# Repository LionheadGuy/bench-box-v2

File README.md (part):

# Bench Box V2

A portable, battery-powered workstation built around an **ODROID-H5** and a **10.1" touchscreen** in a 3D-printed
case with a carry handle. Think of it as a chunky, repairable laptop: USB-C charging, about 3 hours on its own battery,
its own USB 3 hub, WiFi 6E, optional LTE, and a dock for an Elgato Stream Deck module.

It was made for developing car infotainment systems on the bench (it runs the same x86 computer the car does), but
nothing in it is car-specific: it is a general-purpose Windows or Linux PC.

| | |
|---|---|
| Computer | ODROID-H5 (Intel Core i3-N300, 8 cores), 16 GB DDR5, NVMe SSD |
| Screen | 10.1" 1280 x 800 IPS touchscreen, flush in the front frame |
| Battery | 14.8 V 6.6 Ah LiPo (~98 Wh) with a smart BMS; ~3 h at a typical 30 W |
| Charging | USB-C PD (60 W+ charger; 100 W for the fastest charge), runs while charging, no break when unplugged |
| USB | 4 x USB-A on the back: three on the box's own hub board, one wired straight through to a spare port on the computer; plus header ports used inside for the Stream Deck |
| Network | Ethernet on a keystone jack in the back wall |
| Wireless | WiFi 6E + Bluetooth (Intel AX210); optional LTE Cat 6 (Quectel EM060K); optional Bluetooth hands-free board (calls, phone book, phone audio) |
| Cooling | 3 Noctua fans (one in, two out), on the H5's own fan control |
| Size | about 280 x 227 x 116 mm (W x H x D, Stream Deck dock included) + 44 mm handle |
| Weight | about 2.7 kg (estimate) |

> ## Status: read this first
>
> **The design is complete, but this exact version has not been built yet.** The first version of the box (same
> computer, screen, fans and mounting, mains-powered) was printed and works. Version 2 adds the battery, the custom
> charger and converter boards, a new hub and a new shell; its parts have been checked against each other in CAD
> (no collisions) but not printed or wired up. The custom boards are designed and checked against their datasheets,
> not yet built; they will be available from the builder, assembled (price to be announced). This page will be updated
> as the first V2 is built.
>
> **Lithium safety**: the pack is a large LiPo with no protection of its own. Never connect it without the BMS, keep
> it in a fireproof LiPo sleeve, charge it where you can watch it until you trust the build, and test new boards on a
> current-limited bench supply first.

## Pictures (CAD)

| Back | Inside (shell hidden, from behind) |
|---|---|
|  |  |

## What's here

| Folder | What |
|---|---|
| [`print/`](print) | **Slicer-ready `.3mf` files**, one per print job, parts already laid flat |
| [`stl/`](stl) | the same parts as STL, in their assembled positions (GitHub shows them in 3D) |
| [`bom.csv`](bom.csv) | the parts list below as a spreadsheet |
| [`wiring/`](wiring) | wiring poster (`bench-box-v2-poster.png` / `.pdf`) and wire-by-wire sheets (open `index.html`; `wirelist.csv` lists every lead) |
| [`images/`](images) | the pictures on this page |

## Bill of materials

**Roughly $1,350 for the core build's bought parts** (estimate, without the screen's price, which varies, and without
the custom boards, whose price is to be announced), plus about $140 for the Stream Deck dock and $150 for LTE. Prices are approximate (USD, November 2026) and change; links are to the maker or a major seller. "x2" etc. is how
many the box uses.

### Computer

| Part | Qty | For | Price | Notes |
|---|---|---|---|---|
| [Hardkernel ODROID-H5](https://www.hardkernel.com/shop/odroid-h5/) | 1 | the computer | $230 | no power adapter needed; ships from Korea |
| [16 GB DDR5 SODIMM (Corsair CMSX16GX5M1A5600C48)](https://www.centralcomputer.com/corsair-cmsx16gx5m1a5600c48-16gb-16gbx1-ddr5-so-dimm-laptop-memory.html) | 1 | RAM | ~$220-250 | any single DDR5 SODIMM works; runs at 4800 |
| [M.2 2280 NVMe SSD (SanDisk Optimus 5100 500 GB)](https://www.cdw.com/product/sandisk-optimus-5100-ssd-500-gb-pcie-4.0-x4-nvme/9205163) | 1 | storage, slot M2_SSD1 | ~$118 | any M.2 2280 NVMe |
| [Intel AX210NGW WiFi 6E + Bluetooth card](https://www.amazon.com/dp/B08MJLPZPL) | 1 | WiFi | ~$20-25 |  |
| [M.2 M-key to A/E-key adapter (HighZer0)](https://www.amazon.com/dp/B0BGCWQY67) | 1 | puts the AX210 in slot M2_SSD4 | ~$12-15 | the H5 has only M-key slots |
| [Tenmory WiFi 6E antenna kit (2 RP-SMA antennas + 2 MHF4 pigtails)](https://www.amazon.com/dp/B07QDZKH5N) | 1 | WiFi antennas | ~$15 | pigtails go to the back-wall WiFi holes |

### Screen and controls

| Part | Qty | For | Price | Notes |
|---|---|---|---|---|
| [VIEWMEI 10.1" 1280 x 800 USB-C touchscreen](https://www.amazon.com/dp/B0GCNXNZ17) | 1 | main screen | check listing | the frame is sized to this screen: 245.5 x 168.75 x 21.5 mm, 75 mm VESA (M4). Check the size before buying |
| [12 mm momentary metal push button, 5 V ring LED](https://www.amazon.com/s?k=12mm+momentary+metal+push+button+5V+ring+LED) | 1 | power button | ~$5-8 | 11.75 mm hole; NO contacts + LED |
| [KCD1 rocker switch, 20 A (Dopkiut, 10-pack)](https://www.amazon.com/dp/B0HCZ5X637) | 1 | master power switch | $6 | 19.2 x 12.7 mm cut-out |

### Battery and charging

| Part | Qty | For | Price | Notes |
|---|---|---|---|---|
| [Liperior Endurance 6600 mAh 4S2P LiPo (LPD66004S150)](https://rcbattery.com/liperior-endurance-6600mah-4s2p-150c-14-8v-speed-runs-lipo-battery.html) | 1 | the pack, ~98 Wh | $69.99 | 135 x 54 x 42 mm, bare 7 AWG leads, no protection of its own |
| [JBD SP04S010A smart BMS, 4S, NMC / Li-ion version, 20 A or 30 A](https://jbdbms.com/products/sp04s010a) | 1 | protection and balancing | ~$17.50 | pick the NMC (Li-ion) 4S version; add the Bluetooth module for the phone app |
| [LiPo safety bag (DerBlue, 185 x 75 x 60 mm)](https://www.amazon.com/dp/B01GCHBQJS) | 1 | fire sleeve round the pack | ~$8-10 |  |
| [Inline ATC/ATO fuse holder, 14 AWG, + 10 A fuse](https://www.amazon.com/s?k=inline+ATC+fuse+holder+14+AWG) | 1 | pack + lead | ~$6 |  |
| [Semitec 103AT-2 10 k NTC thermistor](https://www.digikey.com/en/products/result?keywords=103AT-2) | 1 | pack temperature for the charger | $0.68 | tape it to the pack |
| [JST PH 2-pin pigtails (pack of 10)](https://www.amazon.com/s?k=JST+PH+2.0+2+pin+pigtail) | 1 | NTC to charger J4 | ~$6 |  |
| [Amass XT30-U connector pairs (5 pairs)](https://www.getfpv.com/amass-xt30-u-lipo-connector-set-5-pairs.html) | 1 | all power leads | ~$8 |  |
| [100 W USB-C PD charger (Anker Prime 100 W or UGREEN Nexode 100 W)](https://www.amazon.com/dp/B0963HDMJP) | 1 | charges and runs the box | ~$50-70 | any USB-C PD charger with 20 V; 60 W minimum |
| [USB-C cable, 5 A e-marked (Anker 100 W)](https://www.amazon.com/dp/B072JYDQ7N) | 1 | charger to box | ~$15-20 | needed for the 100 W setting (JP1 cut) |

### Custom boards (from the builder)

Designed for this box and sold assembled by the builder; prices are to be announced. What each board does and how it
connects: [Custom boards](#custom-boards) below.

| Part | Qty | For | Price | Notes |
|---|---|---|---|---|
| Hub board | 1 | the USB ports on the back, and the battery readout | TBD | from the builder |
| Charger board | 1 | USB-C in, charging, power path | TBD | from the builder |
| Converter board | 1 | fuses + 12 V for the H5 | TBD | from the builder; fuses not included (below) |
| [Littelfuse 0297010.WXNV MINI blade fuse, 10 A](https://www.digikey.com/en/products/result?keywords=0297010.WXNV) | 1+ | converter board F2 | $0.39 | buy spares |
| [Littelfuse 0297005.WXNV MINI blade fuse, 5 A](https://www.digikey.com/en/products/result?keywords=0297005.WXNV) | 1+ | converter board F1 | $0.39 | buy spares |

### USB and cables

| Part | Qty | For | Price | Notes |
|---|---|---|---|---|
| [HDMI, 1 ft, 90 degree plug](https://www.amazon.com/dp/B06Y69TCTW) | 1 | H5 to screen | ~$8-10 |  |
| [USB-A to USB-C, 1 ft, right-angle (2-pack)](https://www.amazon.com/dp/B0784F9JP2) | 1 | H5 USB 2.0 to the screen (power + touch), and H5 USB 3.0 to the hub board | ~$8 | the 2-pack covers both |
| [USB-A to JST PH 4-pin lead](https://www.amazon.com/s?k=usb+a+to+jst+ph+4+pin+cable) | 1 | the back's pass-through port to a spare H5 USB 2.0 port | ~$5 | check the lead's pin order against the board before plugging it in |
| [18 AWG pigtail, 5.5 x 2.1 mm male barrel (3-pack)](https://www.amazon.com/dp/B0DGQS55NG) | 1 | converter 12 V to the H5 | $6.99 | fit an XT30 male on the free end |
| [Cat6 UTP punch-down keystone jack](https://www.amazon.com/s?k=cat6+utp+punch+down+keystone+jack) | 1 | Ethernet port in the back wall | ~$5 | standard keystone (14.9 x 19.4 mm opening); unshielded |
| [Cat6 patch cable, 1 ft](https://www.amazon.com/s?k=cat6+patch+cable+1+ft) | 1 | H5 to the keystone jack | ~$5 | far end cut off and punched down on the jack |
| [JST PH 4-pin lead, 200 mm](https://www.amazon.com/s?k=jst+ph+2.0+4+pin+cable) | 1 | hub board to the BMS's UART plug (battery readout) | ~$5 | check the BMS's pin order before plugging it in |

### Cooling

| Part | Qty | For | Price | Notes |
|---|---|---|---|---|
| [Noctua NF-A9x14 PWM](https://www.amazon.com/dp/B009NQM7V2) | 1 | intake, back wall | $18.95 |  |
| [Noctua NF-A6x15 PWM (12 V version)](https://www.amazon.com/dp/B0DJNX4CX4) | 2 | exhaust, top | $16.95 each | not the 5 V version |
| [Noctua 3-way 4-pin PWM splitter (NA-SC1)](https://www.amazon.com/dp/B0DJPBXZ89) | 1 | three fans on the H5 fan header | ~$10 |  |

### Screws, inserts, small parts

| Part | Qty | For | Price | Notes |
|---|---|---|---|---|
| [ruthex M3 heat-set inserts (100)](https://www.amazon.com/dp/B08BCRZZS3) | 33 used (37 with the Bluetooth board) | all M3 mounts | $9.99 | 4.0 mm holes as printed |
| [ruthex M2 heat-set inserts](https://www.amazon.com/dp/B088QJG676) | 8 used | BMS + modem | ~$9-10 |  |
| [M3 button-head screw kit (Besitu, 6-35 mm)](https://www.amazon.com/dp/B0D1KQCBMT) | 1 | M3 x 6 (8), x 8 (17, +4 for the Bluetooth board), x 10 (8) | $21.99 | button heads: the holes have no countersinks |
| [M4 x 8 button-head screws](https://www.amazon.com/dp/B0FGX64FW2) | 4 | screen VESA | ~$21 (kit) | check the screen's thread depth first |
| [M2 screws: 4 x M2 x 6 + 4 long (length to suit the BMS)](https://www.amazon.com/s?k=M2+button+head+screw+kit) | 8 | modem board, BMS | ~$10 | BMS screws go through cover, board and base plate |
| [Hook-and-loop straps, 20 mm wide](https://www.amazon.com/s?k=20mm+hook+and+loop+battery+strap) | 2 | hold the pack | ~$7 |  |
| [Stick-on rubber feet](https://www.amazon.com/dp/B07PWCC6KP) | 4 | under the feet | $7.99 |  |

### Wire and connectors

| Part | Qty | For | Price | Notes |
|---|---|---|---|---|
| [14 AWG silicone wire, red + black](https://www.amazon.com/s?k=14+awg+silicone+wire+red+black) | 1 | battery path | ~$12 |  |
| [18 AWG silicone pair, tinned copper (BNTECHGO)](https://www.amazon.com/dp/B0779QRR58) | 1 | hub and 12 V leads | $14.83 |  |
| [Dupont crimp kit (housings + pins + crimper)](https://www.amazon.com/s?k=dupont+crimp+kit) | 1 | header connections | ~$25 |  |
| [Heat-shrink kit](https://www.amazon.com/dp/B0C81FHPHN) | 1 | every joint | $9.99 |  |

### Printing

| Part | Qty | For | Price | Notes |
|---|---|---|---|---|
| [ASA or ABS filament, 1 kg](https://www.amazon.com/s?k=ASA+filament+1kg) | 1 | all printed parts | ~$25 | PETG for a desk-only box |

### Optional: Stream Deck dock

| Part | Qty | For | Price | Notes |
|---|---|---|---|---|
| [Elgato Stream Deck Module 15 Keys (10GBT9901)](https://www.elgato.com/us/en/p/stream-deck-module-15-keys) | 1 | 15 LCD keys, docked on the right wall | $129.99 | case (122 x 83 x 24 mm): print/5-stream-deck-case.3mf + 4 x M3 x 6 and 4 inserts |
| [Coiled USB-C to USB-A cable (Cable Matters 4 ft)](https://cablematters.com/pc-1678-123-coiled-usb-c-to-usb-a-charging-cable-4ft.aspx) | 1 | Stream Deck to header port P7 | ~$10-13 | USB-A end cut off; thread the bare wires through the case and the shell before crimping them, as both holes are printed small |

### Optional: LTE

| Part | Qty | For | Price | Notes |
|---|---|---|---|---|
| [Quectel EM060K-GL LTE Cat 6 M.2 module](https://www.waveshare.com/product/em060k-gl.htm) | 1 | mobile data | $98.99 |  |
| [Waveshare USB to M.2 B-key board](https://www.waveshare.com/usb-to-m.2-b-key.htm) | 1 | carries the module (USB) | ~$22 | CUT 58 mm from its USB end (removes its SMA jacks) to fit the mount; file the edge and check for shorts |
| LTE modem board (coming) | 1 | the builder's own carrier for the module, in place of the Waveshare board | TBD | from the builder; same size and holes as the cut Waveshare board, so it uses the same four standoffs (JST end up); USB on a JST PH 4-pin lead, no USB-A plug or extension |
| [MHF4 to SMA female bulkhead pigtails, 20 cm (2-pack)](https://www.amazon.com/dp/B0FVW7M3LC) | 1 | module to the back-wall LTE holes | $7.49 |  |
| [LTE antennas, SMA male](https://www.amazon.com/s?k=LTE+antenna+SMA+male) | 2 | on the LTE holes | ~$15 |  |
| Nano SIM with a data plan that allows modems | 1 |  |  | many phone plans do not allow modem use |

### Optional: Bluetooth hands-free board

| Part | Qty | For | Price | Notes |
|---|---|---|---|---|
| Bluetooth board | 1 | phone calls, phone book and phone music (Feasycom FSC-BT1026C module), as a COM port + a USB sound card on one USB lead | TBD | from the builder |
| [JST PH 2.0 pigtails, 2 / 3 / 4-pin (assorted)](https://www.amazon.com/s?k=JST+PH+2.0+pigtail+assortment) | 1 set | the board's USB lead (4-pin, to header port P6), mic (2-pin) and line out (3-pin) | ~$8 | |
| [3.5 mm stereo panel-mount socket, M6 nut](https://www.amazon.com/s?k=3.5mm+panel+mount+stereo+jack+socket) | 2 | mic in + line out on the back wall | ~$6 | 6.5 mm holes as printed; check the thread before printing |
| [Hands-free car-kit microphone, 3.5 mm plug](https://www.amazon.com/s?k=car+hands+free+microphone+3.5mm) | 1 | the call microphone | ~$8-10 | plugs into the mic socket on the back |

### Optional: dash screen

| Part | Qty | For | Price | Notes |
|---|---|---|---|---|
| [ROADOM 10.25" 1920 x 720 bar touchscreen](https://www.amazon.com/dp/B0H9RBHD2X) | 1 | second screen for gauge / dashboard layouts | check listing | its printed case and a video pass-through in the box are coming |

## Custom boards

Sold assembled by the builder (prices to be announced). They are designed and checked, **not yet built or tested**:
test the first ones on a current-limited bench supply, without the pack, before they go in a box.

**Hub board** (75.5 x 68 mm). The box's USB ports and the battery readout on one board, in place of an
off-the-shelf hub.

- **Three USB-A ports** on the back, from a 4-port USB 3.2 hub chip, each with its own current limit.
- **Upstream on USB-C**, to the computer's USB 3.0 port.
- **A fourth USB-A on the back is a pass-through**: it is not on the hub at all, only wired to a 4-pin plug inside, so
  one device (an audio interface, say) can run straight to a spare port on the computer instead of sharing the hub.
- **The battery readout is on the board**: an isolated USB-serial port with a 4-pin plug for the BMS's UART, so there
  is no dongle and no cut extension lead inside the box.
- **5 V for the ports is made on the board** from the box's 12-20.5 V rail.

**Charger board** (52 x 68 mm). USB-C in, battery charging and the box's power path, in place of a USB-C PD trigger, a
separate 4S charger and two ideal-diode modules.

- **USB-C in at 20 V**: asks any USB-C PD charger for 20 V.
- **4S lithium charging** at **16.4 V** (4.10 V per cell, kinder to a pack that is kept full) and **4.5 A**.
- **Input current limit**: it turns the charging down so the box (running + charging) never overloads the charger.
  As supplied **2.92 A** (any 60 W+ charger, any normal cable); **cut jumper JP1** for **4.38 A** (needs a 100 W charger
  AND a 5 A e-marked USB-C cable).
- **Power path**: the box runs from SYS out, from USB-C when plugged in and from the pack when not, with no break.
- **Battery temperature**: a 10 k NTC (103AT) taped to the pack, into J4, gives a 0-45 °C charge window. **It will not
  charge with nothing in J4.** For a bench test without the NTC, close JP2 (fixed 10 k; removes the temperature cut-out).
- **LEDs**: green = 20 V agreed, yellow = input OK, red = charging, green = full (all dark when running on the pack).
- **Connectors** (plugs from above): J1 USB-C (through the left wall), J2 XT30 male = battery (through the BMS and the
  pack fuse), J3 XT30 female = SYS out to the rocker switch, J4 NTC (JST PH 2-pin).
- Charge time, 6.6 Ah pack: about 1.5 h with the box off (JP1 cut, 100 W charger) or 2.5 h (as supplied).

**Converter board** (70 x 60 mm). Splits the power rail and makes the computer's 12 V.

```
IN (XT30 male, 12-21 V from the rocker switch)
 ├─ 5 A MINI blade fuse ──────────────────> HUB (XT30 female) -> USB hub power (7-24 V)
 └─ 10 A MINI blade fuse -> 12 V 5 A DC/DC -> 12 V OUT (XT30 female) -> ODROID-H5   ("12 V ON" LED)
```

The fuses are MINI (ATM) automotive blades, replaceable by hand; buy them separately (in the BOM).

**Bluetooth board** (optional, 60 x 48 mm). Phone calls, phone book and phone music on one USB lead to the H5: a
Feasycom FSC-BT1026C module, a COM port for its commands (no driver on Windows 10/11) and a USB sound card whose
input carries the phone's audio into the computer (the H5 has no audio input) and whose output is a spare line out.
Connectors (JST PH): J2 USB lead (1 = +5 V, 2 = D-, 3 = D+, 4 = GND), J3 cabin microphone (electret, 1 = +), J4 line
out (L, R, GND); J1 USB-C as an alternative to J2 (use one, not both). LEDs: blue blinks while pairing, green when
connected. Keep metal away from the module's antenna at the top edge.

**LTE modem board** (optional, coming). A carrier for the Quectel EM060K: the module plugs into its M.2 socket, a
nano-SIM holder sits beside it, and USB comes in on a JST PH 4-pin lead (1 = +5 V, 2 = D-, 3 = D+, 4 = GND), so there is
no USB-A plug or extension in the box. The antennas still clip onto the module itself. Same size (30 x 58 mm) and
holes as the cut Waveshare board; the SIM holder is on its back.

| Top | Back |
|---|---|
|  |  |

**All boards**: XT30 polarity: + is the **square end** of the housing; check with a meter before the first plug-in.
Mounting: M3 screws onto heat-set inserts in the printed box (M2 for the modem board).

## Printing

Any FDM printer. **The shell needs a bed of at least 285 x 230 mm** (a 300 mm class printer such as a Bambu H2D,
Prusa XL or a large Voron); everything else fits a 256 x 256 mm bed.

**Material: ASA or ABS** (the box gets warm inside and may sit in a car). PETG works for a desk-only box. PLA is not
recommended (softens around 55 °C). 0.2 mm layers, 4 walls, 15-25 % infill. About one 1 kg spool in all (estimate).

| File | Parts | Supports | Notes |
|---|---|---|---|
| `1-shell.3mf` | the shell (frame, walls, battery bay, mounts) | **yes, on build plate only** | prints on its back; the biggest print, roughly 7-9 h |
| `2-front-plate.3mf` | front plate (holds the screen and the H5) | no | face down |
| `3-handle-and-feet.3mf` | handle + 2 feet | no | on their sides |
| `4-screen-button-caps.3mf` | 5 screen button caps | try without; tree supports if the small lugs droop | tiny parts: brim helps |
| `5-stream-deck-case.3mf` | Stream Deck case tray + front frame | no | optional (only with the Stream Deck) |
| `6-stream-deck-cradle-test.3mf` | a piece of the shell's right wall with the Stream Deck cradle | yes | optional: print it first to check your Stream Deck case slides in before printing the whole shell |
| `7-keystone-test.3mf` | a piece of the shell's back wall with the Ethernet keystone frame | no | optional: print it first to check your keystone jack clips in, as makes differ slightly |

After printing: ream the Stream Deck cable holes to your cable - both the one in the case and the 4 mm one in the
shell's right wall are printed small on purpose - and clean up the screen button holes so the caps turn freely.

## Assembly

Tools: soldering iron with a heat-set insert tip, small screwdrivers / 2 mm hex key, Dupont crimper, wire stripper,
multimeter.

1. **Heat-set inserts.** M3: front plate (4 on the H5 standoffs, 5 in the screw tabs), shell (4 hub standoffs on the
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
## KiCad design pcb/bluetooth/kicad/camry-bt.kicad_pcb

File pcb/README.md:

# Custom boards

Three small boards made for the Bench Box V2 (the Bluetooth board is optional). Both are designed to be **made and assembled by PCBWay** (turnkey): every
part has an exact manufacturer part number in the BOM, so you upload three files and they build it.

> **Status: designed and checked in KiCad (ERC clean, DRC 0 errors, 0 unconnected), checked against the datasheets,
> but not yet built or tested.** The charger board charges a lithium pack. Have someone who knows power electronics
> look over the schematic before you order, and test the first board on a bench supply with a current limit, without the
> pack, before it goes in a box.

## Charger board (`charger/`)

USB-C in, battery charging and the box's power path, in one 52 x 68 mm board. It replaces a USB-C "PD trigger" module,
a separate 4S charger and two ideal-diode modules.

- **USB-C in at 20 V** (WCH CH224A asks any USB-C PD charger for 20 V).
- **4S lithium charging** (TI BQ24610): **16.4 V** (4.10 V per cell, kinder to a pack that is kept full), **4.5 A**
  charge, 0.3 A precharge and end of charge, ~9 h safety timer.
- **Input current limit**: the board measures the total current from the USB-C charger (box running + charging) and
  turns the charging down to stay under the limit, so the box can never overload the charger.
  - **As built: 2.92 A** (any 60 W+ USB-C charger, any normal cable).
  - **Cut jumper JP1: 4.38 A** (needs a 100 W charger AND a 5 A e-marked USB-C cable).
- **Power path**: the box runs from the board's SYS output: from USB-C when plugged in, from the pack when not, with no
  break in between.
- **Battery temperature**: a 10 k NTC (103AT) taped to the pack, into J4 (JST PH 2-pin), gives a 0-45 °C charge
  window. **It will not charge with nothing in J4.** For a bench test without the NTC, close JP2 (fixed 10 k; this
  removes the temperature cut-out).
- **LEDs**: green = 20 V agreed, yellow = input OK, red = charging, green = full (all dark when running on the pack).
- **Connectors** (all vertical, plugs from above): J1 USB-C (through the box's left wall), J2 XT30 male = battery
  (through the BMS and the pack fuse), J3 XT30 female = SYS out to the power switch, J4 NTC.
- Charge time, 6.6 Ah pack: about 1.5 h with the box off (JP1 cut, 100 W charger) or 2.5 h (as built); longer while
  the box runs.

### Ordering at PCBWay (PCB + assembly)

Upload `charger-gerbers.zip`, `charger-bom-pcbway.csv`, `charger-positions.csv`.

| Option | Value |
|---|---|
| Size / layers | 68 x 52 mm, **4 layers**, FR-4 TG150-160, 1.6 mm |
| Min track / spacing | **5 / 5 mil** |
| Min hole | **0.2 mm** |
| Copper | **1 oz outer, 1 oz inner** (do not pick 2 oz: the layout is at 5 mil) |
| Surface finish | **ENIG** |
| Vias | tented |
| Assembly | yes, top side; 63 SMD + 3 through-hole parts (both XT30s, the JST) |

Parts with no DigiKey/Mouser listing (CH224A, HRO USB-C socket, AMASS XT30s) have their LCSC numbers in the BOM;
PCBWay buys from Shenzhen suppliers first. Plain resistors and capacitors may be swapped for equivalents; everything
marked "exact part only" may not.

## Converter board (`converter/`)

Splits the power rail and makes the computer's 12 V. 70 x 60 mm, 2 layers.

```
IN (XT30 male, 12-21 V from the power switch)
 ├─ 5 A MINI blade fuse ──────────────────────────────> HUB (XT30 female) -> USB hub power (7-24 V)
 └─ 10 A MINI blade fuse -> 220 uF + 24 V TVS -> TRACO TEN 60-2412WIN -> 12 V OUT (XT30 female) -> ODROID H5
                                                                       └─ "12 V ON" LED
```

- TRACO TEN 60-2412WIN: 9-36 V in, 12 V 5 A out, isolated, with TRACO's recommended input and output parts.
- Fuses are MINI (ATM) automotive blades in holders, replaceable by hand. **Buy them separately** (they are not in the
  assembly BOM): Littelfuse **0297010.WXNV** (10 A) and **0297005.WXNV** (5 A).

### Ordering at PCBWay

Upload `converter-gerbers.zip`, `converter-bom-pcbway.csv`, `converter-positions.csv`. 2 layers, 1.6 mm, 1 oz, ENIG,
0.3 mm minimum gap, 0.4 mm minimum hole: any standard 2-layer option. Order it together with the charger board to share
set-up and shipping.

## Bluetooth board (`bluetooth/`)

Optional. Phone calls, phone book and phone music for the box, on one USB lead to the H5. 60 x 48 mm, 4 layers.

- **Module**: Feasycom **FSC-BT1026C** (Bluetooth 5.1, hands-free, phone book, music), soldered to the board, antenna
  at the top edge (keep metal away from it).
- **USB hub** (Microchip USB2514Bi) with three devices behind it: a **COM port** (Microchip MCP2221A, no driver on
  Windows 10/11) for the module's text commands, a **USB sound card** (TI PCM2900C) whose **input** carries the phone's
  music and calls into the computer (the H5 has no audio input of its own) and whose output is a spare **line out**
  (J4), and the module's own USB.
- **Connectors** (JST PH, vertical): J2 USB lead (1 = +5 V, 2 = D-, 3 = D+, 4 = GND), J3 cabin microphone (electret,
  1 = +), J4 line out (L, R, GND); J1 USB-C as an alternative to J2 (use one, not both).
- LEDs: blue blinks while pairing, green when connected.

### Ordering at PCBWay (PCB + assembly)

Upload `bt-gerbers.zip`, `bt-bom-pcbway.csv`, `bt-positions.csv`. 60 x 48 mm, **4 layers**, 1.6 mm, 1 oz, ENIG,
**5 / 5 mil**, **0.2 mm** minimum hole, tented vias; assembly top side, 111 SMD + 3 through-hole parts (the JSTs).
Feasycom offers to review a schematic that uses their module (for Bluetooth range): worth sending `bt-schematic.pdf`
first.

## All three boards

- **XT30 polarity**: + is the **square end** of the housing (pin 2 in KiCad). Check with a meter before the first
  plug-in.
- Mounting: four M3 holes each, onto heat-set inserts in the printed box, M3 x 8 screws.
- `kicad/` holds the KiCad 10 projects (open `*.kicad_pro`), and `*-schematic.pdf` is the printed schematic.

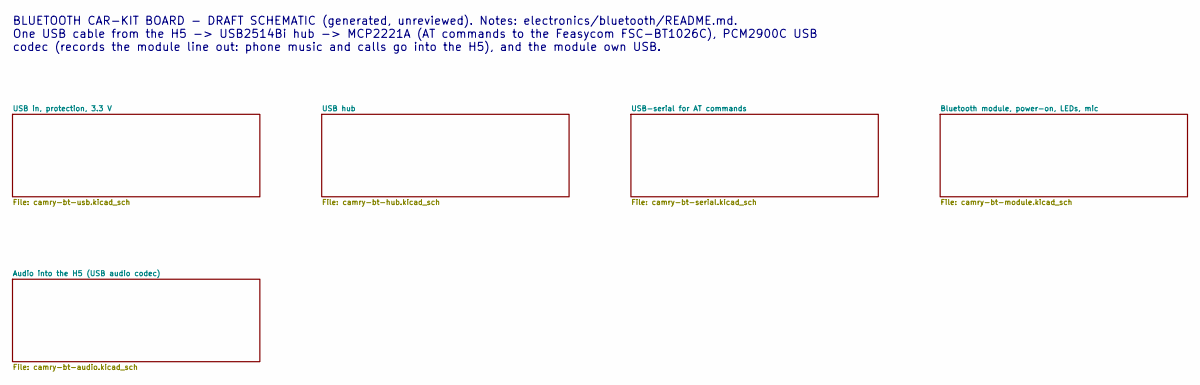
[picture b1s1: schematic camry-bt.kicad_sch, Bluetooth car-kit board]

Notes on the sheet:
BLUETOOTH CAR-KIT BOARD - DRAFT SCHEMATIC (generated, unreviewed). Notes: electronics/bluetooth/README.md. One USB cable from the H5 -> USB2514Bi hub -> MCP2221A (AT commands to the Feasycom FSC-BT1026C), PCM2900C USB codec (records the module line out: phone music and calls go into the H5), and th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

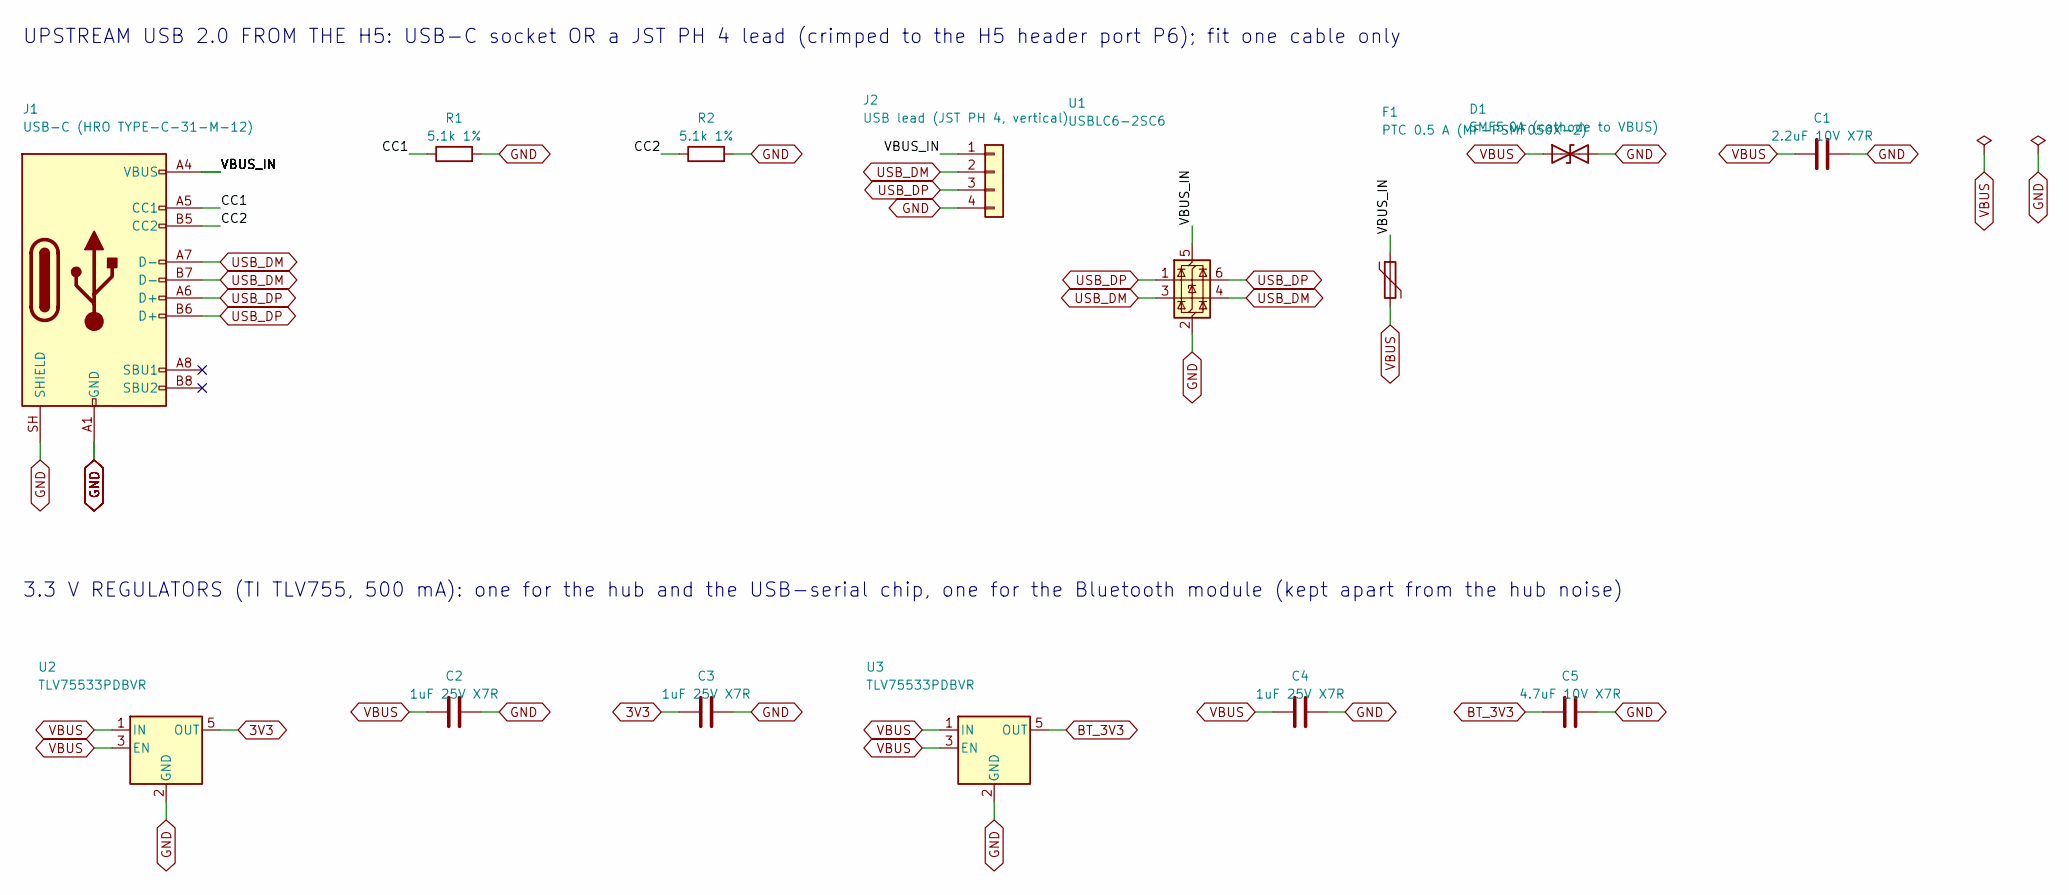
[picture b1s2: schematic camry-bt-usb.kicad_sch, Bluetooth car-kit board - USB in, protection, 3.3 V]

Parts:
C1: 2.2uF 10V X7R; C_0603_1608Metric; MPN GRM188R71A225KE15D
C2, C3, C4: 1uF 25V X7R; C_0603_1608Metric; MPN GRM188R71E105KA12D
C5: 4.7uF 10V X7R; C_0805_2012Metric; MPN GRM21BR71A475KA73L
D1: SMF5.0A (cathode to VBUS); D_SOD-123F; MPN SMF5.0A
F1: PTC 0.5 A (MF-PSMF050X-2); Fuse_0805_2012Metric; MPN MF-PSMF050X-2
J1: USB-C (HRO TYPE-C-31-M-12); USB_C_Receptacle_HRO_TYPE-C-31-M-12; MPN TYPE-C-31-M-12; LCSC C165948
J2: USB lead (JST PH 4, vertical); JST_PH_B4B-PH-K_1x04_P2.00mm_Vertical; MPN B4B-PH-K-S(LF)(SN)
R1, R2: 5.1k 1%; R_0402_1005Metric; MPN RC0402FR-075K1L
U1: USBLC6-2SC6; SOT-23-6; MPN USBLC6-2SC6
U2, U3: TLV75533PDBVR; SOT-23-5; MPN TLV75533PDBVR

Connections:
3V3: C3.1, U2.5 (OUT); also elsewhere on the board
/USB in, protection, 3.3 V/CC1: J1.A5 (CC1), R1.1
/USB in, protection, 3.3 V/CC2: J1.B5 (CC2), R2.1
/USB in, protection, 3.3 V/VBUS_IN: F1.1, J1.A4 (VBUS), J1.A9 (VBUS), J1.B4 (VBUS), J1.B9 (VBUS), J2.1, U1.5 (VBUS)
BT_3V3: C5.1, U3.5 (OUT); also elsewhere on the board
GND: C1.2, C2.2, C3.2, C4.2, C5.2, D1.2 (A2), J1.A1 (GND), J1.A12 (GND), J1.B1 (GND), J1.B12 (GND), J1.SH (SHIELD), J2.4, R1.2, R2.2, U1.2 (GND), U2.2 (GND), U3.2 (GND); also elsewhere on the board
USB_DM: J1.A7 (D-), J1.B7 (D-), J2.2, U1.3 (I/O2), U1.4 (I/O2); also elsewhere on the board
USB_DP: J1.A6 (D+), J1.B6 (D+), J2.3, U1.1 (I/O1), U1.6 (I/O1); also elsewhere on the board
VBUS: C1.1, C2.1, C4.1, D1.1 (A1), F1.2, U2.1 (IN), U2.3 (EN), U3.1 (IN), U3.3 (EN); also elsewhere on the board

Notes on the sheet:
UPSTREAM USB 2.0 FROM THE H5: USB-C socket OR a JST PH 4 lead (crimped to the H5 header port P6); fit one cable only
3.3 V REGULATORS (TI TLV755, 500 mA): one for the hub and the USB-serial chip, one for the Bluetooth module (kept apart from the hub noise)

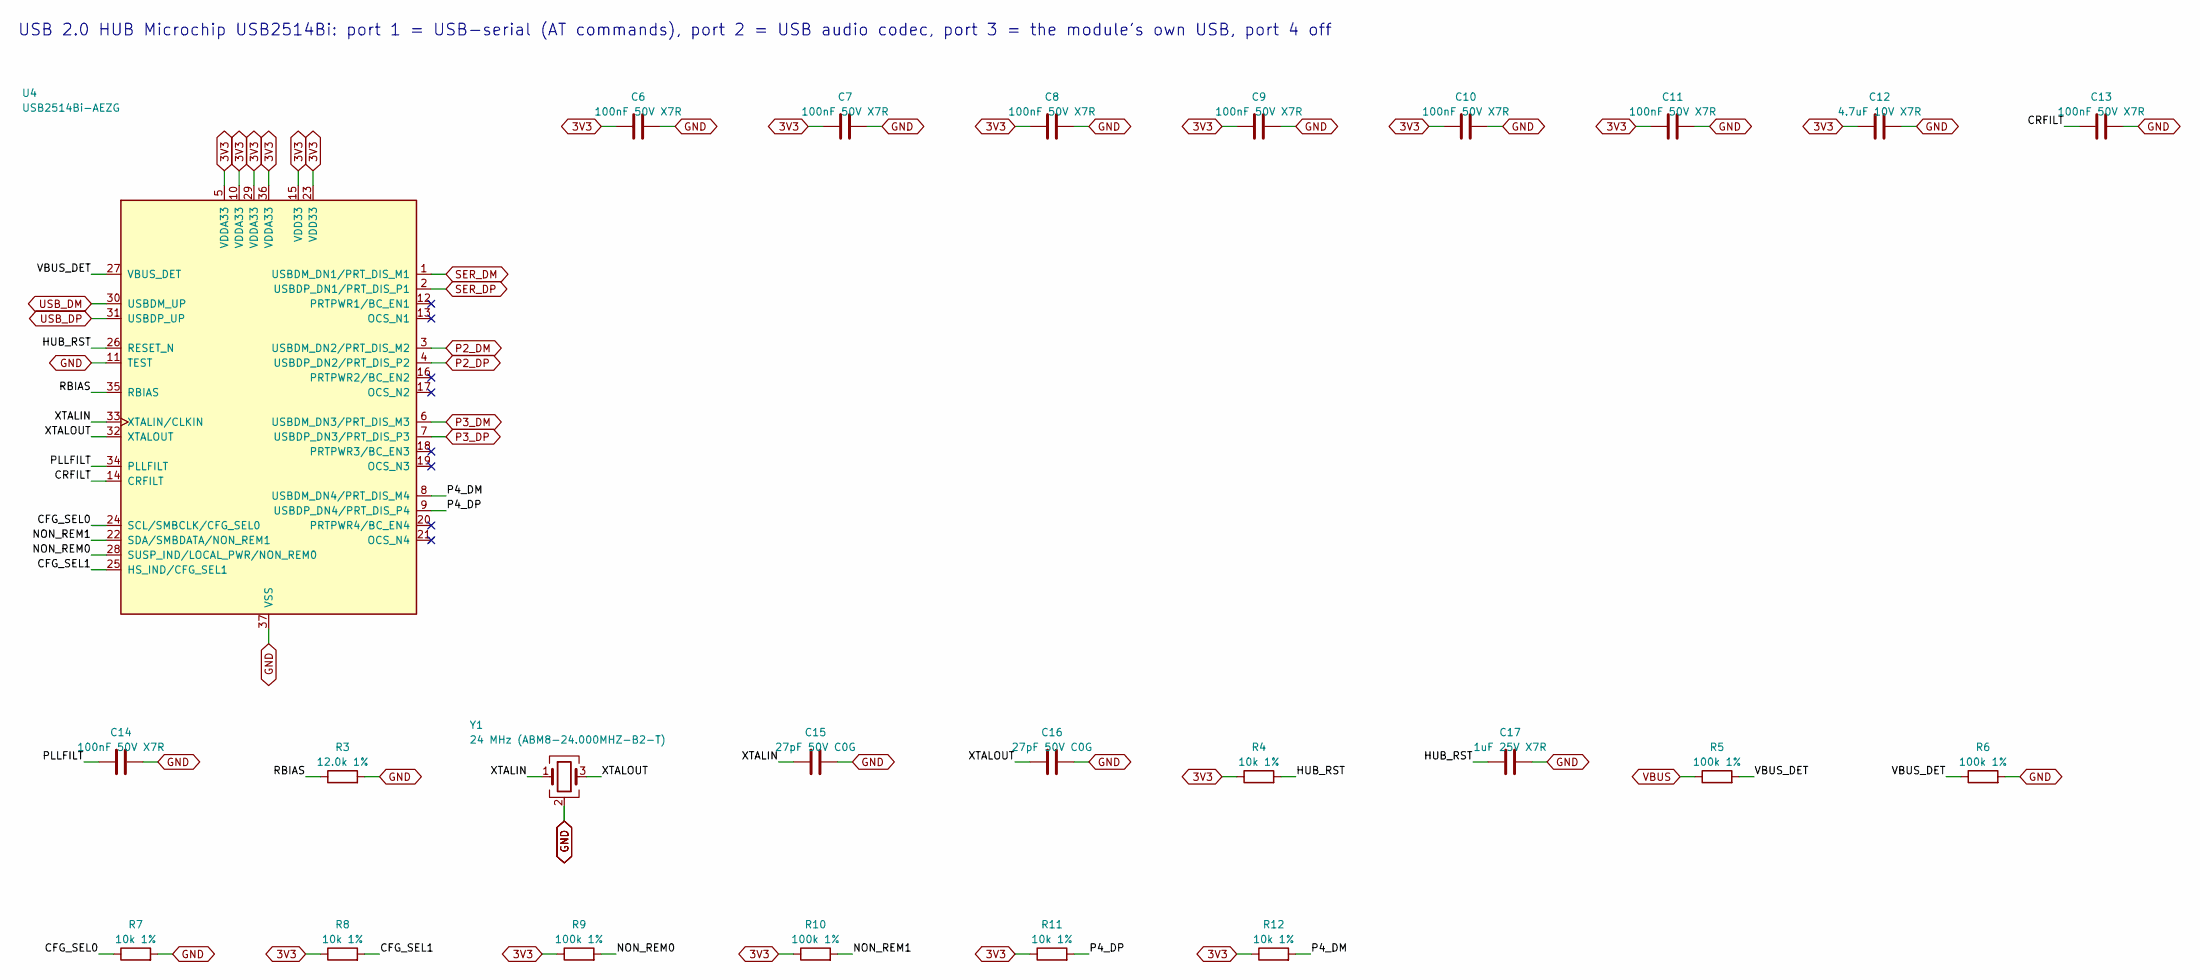
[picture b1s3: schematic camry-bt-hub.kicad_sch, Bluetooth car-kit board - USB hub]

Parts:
C6, C7, C8, C9, C10, C11, C13, C14: 100nF 50V X7R; C_0603_1608Metric; MPN GRM188R71H104KA93D
C12: 4.7uF 10V X7R; C_0805_2012Metric; MPN GRM21BR71A475KA73L
C15, C16: 27pF 50V C0G; C_0603_1608Metric; MPN GRM1885C1H270JA01D
C17: 1uF 25V X7R; C_0603_1608Metric; MPN GRM188R71E105KA12D
R3: 12.0k 1%; R_0402_1005Metric; MPN RC0402FR-0712KL
R4, R7, R8, R11, R12: 10k 1%; R_0402_1005Metric; MPN RC0402FR-0710KL
R5, R6, R9, R10: 100k 1%; R_0402_1005Metric; MPN RC0402FR-07100KL
U4: USB2514Bi-AEZG; QFN-36-1EP_6x6mm_P0.5mm_EP3.7x3.7mm_ThermalVias; MPN USB2514BI-AEZG
Y1: 24 MHz (ABM8-24.000MHZ-B2-T); Crystal_SMD_3225-4Pin_3.2x2.5mm; MPN ABM8-24.000MHZ-B2-T

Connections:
3V3: C6.1, C7.1, C8.1, C9.1, C10.1, C11.1, C12.1, R4.1, R8.1, R9.1, R10.1, R11.1, R12.1, U4.5 (VDDA33), U4.10 (VDDA33), U4.15 (VDD33), U4.23 (VDD33), U4.29 (VDDA33), U4.36 (VDDA33); also elsewhere on the board
/USB hub/CFG_SEL0: R7.1, U4.24 (SCL/SMBCLK/CFG_SEL0)
/USB hub/CFG_SEL1: R8.2, U4.25 (HS_IND/CFG_SEL1)
/USB hub/CRFILT: C13.1, U4.14 (CRFILT)
/USB hub/HUB_RST: C17.1, R4.2, U4.26 (RESET_N)
/USB hub/NON_REM0: R9.2, U4.28 (SUSP_IND/LOCAL_PWR/NON_REM0)
/USB hub/NON_REM1: R10.2, U4.22 (SDA/SMBDATA/NON_REM1)
/USB hub/P4_DM: R12.2, U4.8 (USBDM_DN4/PRT_DIS_M4)
/USB hub/P4_DP: R11.2, U4.9 (USBDP_DN4/PRT_DIS_P4)
/USB hub/PLLFILT: C14.1, U4.34 (PLLFILT)
/USB hub/RBIAS: R3.1, U4.35 (RBIAS)
/USB hub/VBUS_DET: R5.2, R6.1, U4.27 (VBUS_DET)
/USB hub/XTALIN: C15.1, U4.33 (XTALIN/CLKIN), Y1.1
/USB hub/XTALOUT: C16.1, U4.32 (XTALOUT), Y1.3
GND: C6.2, C7.2, C8.2, C9.2, C10.2, C11.2, C12.2, C13.2, C14.2, C15.2, C16.2, C17.2, R3.2, R6.2, R7.2, U4.11 (TEST), U4.37 (VSS), Y1.2 (G), Y1.4 (G); also elsewhere on the board
P2_DM: U4.3 (USBDM_DN2/PRT_DIS_M2); also elsewhere on the board
P2_DP: U4.4 (USBDP_DN2/PRT_DIS_P2); also elsewhere on the board
P3_DM: U4.6 (USBDM_DN3/PRT_DIS_M3); also elsewhere on the board
P3_DP: U4.7 (USBDP_DN3/PRT_DIS_P3); also elsewhere on the board
SER_DM: U4.1 (USBDM_DN1/PRT_DIS_M1); also elsewhere on the board
SER_DP: U4.2 (USBDP_DN1/PRT_DIS_P1); also elsewhere on the board
USB_DM: U4.30 (USBDM_UP); also elsewhere on the board
USB_DP: U4.31 (USBDP_UP); also elsewhere on the board
VBUS: R5.1; also elsewhere on the board

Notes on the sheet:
USB 2.0 HUB Microchip USB2514Bi: port 1 = USB-serial (AT commands), port 2 = USB audio codec, port 3 = the module's own USB, port 4 off

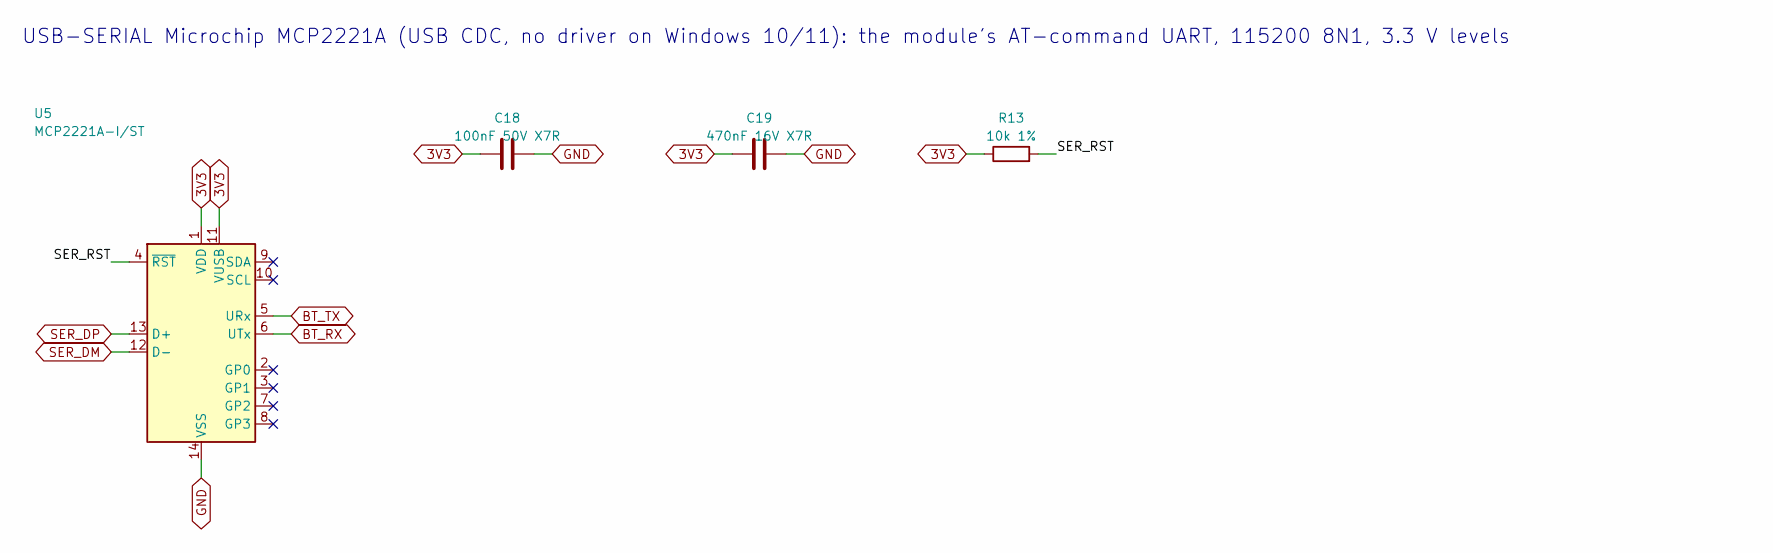
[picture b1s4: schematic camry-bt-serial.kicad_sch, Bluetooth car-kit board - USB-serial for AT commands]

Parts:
C18: 100nF 50V X7R; C_0603_1608Metric; MPN GRM188R71H104KA93D
C19: 470nF 16V X7R; C_0603_1608Metric; MPN GRM188R71C474KA88D
R13: 10k 1%; R_0402_1005Metric; MPN RC0402FR-0710KL
U5: MCP2221A-I/ST; TSSOP-14_4.4x5mm_P0.65mm; MPN MCP2221A-I/ST

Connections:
3V3: C18.1, C19.1, R13.1, U5.1 (VDD), U5.11 (VUSB); also elsewhere on the board
/USB-serial for AT commands/SER_RST: R13.2, U5.4 (~RST)
BT_RX: U5.6 (UTx); also elsewhere on the board
BT_TX: U5.5 (URx); also elsewhere on the board
GND: C18.2, C19.2, U5.14 (VSS); also elsewhere on the board
SER_DM: U5.12 (D-); also elsewhere on the board
SER_DP: U5.13 (D+); also elsewhere on the board

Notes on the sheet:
USB-SERIAL Microchip MCP2221A (USB CDC, no driver on Windows 10/11): the module's AT-command UART, 115200 8N1, 3.3 V levels

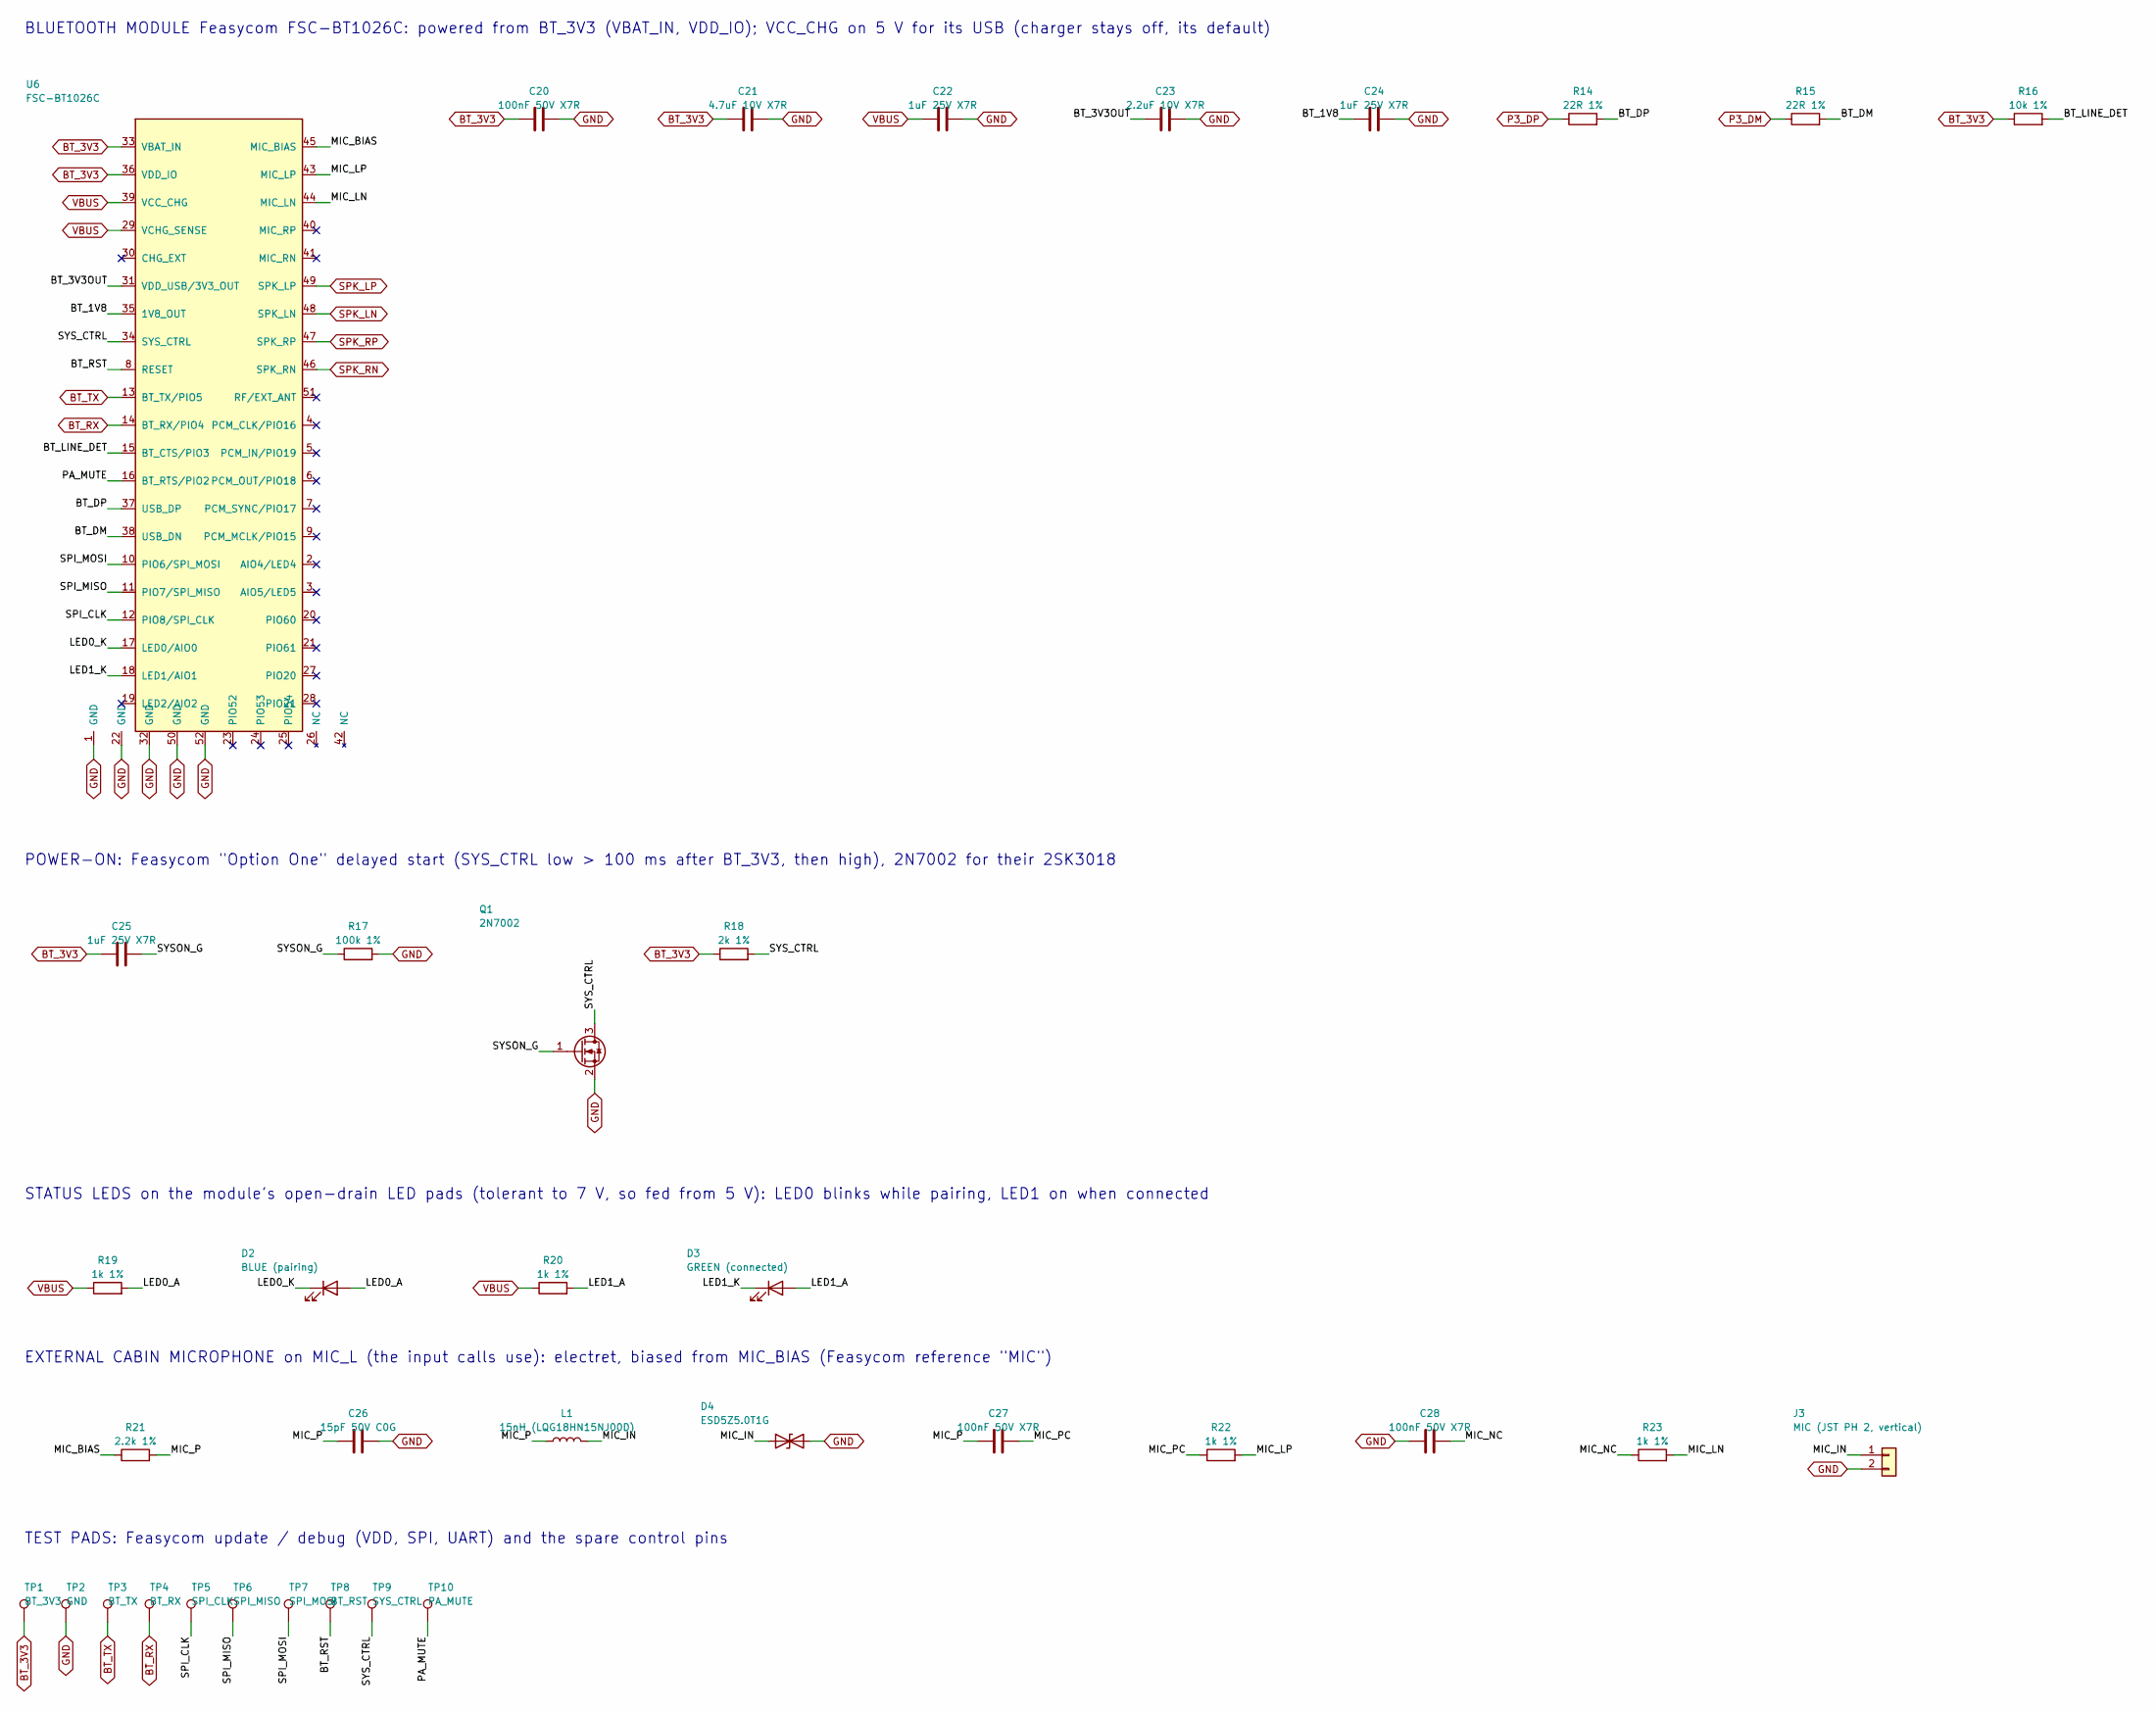
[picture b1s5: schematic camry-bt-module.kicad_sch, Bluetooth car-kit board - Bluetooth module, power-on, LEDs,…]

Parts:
C20, C27, C28: 100nF 50V X7R; C_0603_1608Metric; MPN GRM188R71H104KA93D
C21: 4.7uF 10V X7R; C_0805_2012Metric; MPN GRM21BR71A475KA73L
C22, C24, C25: 1uF 25V X7R; C_0603_1608Metric; MPN GRM188R71E105KA12D
C23: 2.2uF 10V X7R; C_0603_1608Metric; MPN GRM188R71A225KE15D
C26: 15pF 50V C0G; C_0603_1608Metric; MPN GRM1885C1H150JA01D
D2: BLUE (pairing); LED_0603_1608Metric; MPN LTST-C191TBKT
D3: GREEN (connected); LED_0603_1608Metric; MPN LTST-C191KGKT
D4: ESD5Z5.0T1G; D_SOD-523; MPN ESD5Z5.0T1G
J3: MIC (JST PH 2, vertical); JST_PH_B2B-PH-K_1x02_P2.00mm_Vertical; MPN B2B-PH-K-S(LF)(SN)
L1: 15nH (LQG18HN15NJ00D); L_0603_1608Metric; MPN LQG18HN15NJ00D
Q1: 2N7002; SOT-23; MPN 2N7002LT1G
R14, R15: 22R 1%; R_0402_1005Metric; MPN RC0402FR-0722RL
R16: 10k 1%; R_0402_1005Metric; MPN RC0402FR-0710KL
R17: 100k 1%; R_0402_1005Metric; MPN RC0402FR-07100KL
R18: 2k 1%; R_0402_1005Metric; MPN RC0402FR-072KL
R19, R20, R22, R23: 1k 1%; R_0402_1005Metric; MPN RC0402FR-071KL
R21: 2.2k 1%; R_0402_1005Metric; MPN RC0402FR-072K2L
TP1: BT_3V3; TestPoint_Pad_D1.0mm
TP2: GND; TestPoint_Pad_D1.0mm
TP3: BT_TX; TestPoint_Pad_D1.0mm
TP4: BT_RX; TestPoint_Pad_D1.0mm
TP5: SPI_CLK; TestPoint_Pad_D1.0mm
TP6: SPI_MISO; TestPoint_Pad_D1.0mm
TP7: SPI_MOSI; TestPoint_Pad_D1.0mm
TP8: BT_RST; TestPoint_Pad_D1.0mm
TP9: SYS_CTRL; TestPoint_Pad_D1.0mm
TP10: PA_MUTE; TestPoint_Pad_D1.0mm
U6: FSC-BT1026C; Feasycom_FSC-BT1026x; MPN FSC-BT1026C

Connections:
/Bluetooth module, power-on, LEDs, mic/BT_1V8: C24.1, U6.35 (1V8_OUT)
/Bluetooth module, power-on, LEDs, mic/BT_3V3OUT: C23.1, U6.31 (VDD_USB/3V3_OUT)
/Bluetooth module, power-on, LEDs, mic/BT_DM: R15.2, U6.38 (USB_DN)
/Bluetooth module, power-on, LEDs, mic/BT_DP: R14.2, U6.37 (USB_DP)
/Bluetooth module, power-on, LEDs, mic/BT_LINE_DET: R16.2, U6.15 (BT_CTS/PIO3)
/Bluetooth module, power-on, LEDs, mic/BT_RST: TP8.1, U6.8 (RESET)
/Bluetooth module, power-on, LEDs, mic/LED0_A: D2.2 (A), R19.2
/Bluetooth module, power-on, LEDs, mic/LED0_K: D2.1 (K), U6.17 (LED0/AIO0)
/Bluetooth module, power-on, LEDs, mic/LED1_A: D3.2 (A), R20.2
/Bluetooth module, power-on, LEDs, mic/LED1_K: D3.1 (K), U6.18 (LED1/AIO1)
/Bluetooth module, power-on, LEDs, mic/MIC_BIAS: R21.1, U6.45 (MIC_BIAS)
/Bluetooth module, power-on, LEDs, mic/MIC_IN: D4.1 (A1), J3.1, L1.2
/Bluetooth module, power-on, LEDs, mic/MIC_LN: R23.2, U6.44 (MIC_LN)
/Bluetooth module, power-on, LEDs, mic/MIC_LP: R22.2, U6.43 (MIC_LP)
/Bluetooth module, power-on, LEDs, mic/MIC_NC: C28.2, R23.1
/Bluetooth module, power-on, LEDs, mic/MIC_P: C26.1, C27.1, L1.1, R21.2
/Bluetooth module, power-on, LEDs, mic/MIC_PC: C27.2, R22.1
/Bluetooth module, power-on, LEDs, mic/PA_MUTE: TP10.1, U6.16 (BT_RTS/PIO2)
/Bluetooth module, power-on, LEDs, mic/SPI_CLK: TP5.1, U6.12 (PIO8/SPI_CLK)
/Bluetooth module, power-on, LEDs, mic/SPI_MISO: TP6.1, U6.11 (PIO7/SPI_MISO)
/Bluetooth module, power-on, LEDs, mic/SPI_MOSI: TP7.1, U6.10 (PIO6/SPI_MOSI)
/Bluetooth module, power-on, LEDs, mic/SYSON_G: C25.2, Q1.1 (G), R17.1
/Bluetooth module, power-on, LEDs, mic/SYS_CTRL: Q1.3 (D), R18.2, TP9.1, U6.34 (SYS_CTRL)
BT_3V3: C20.1, C21.1, C25.1, R16.1, R18.1, TP1.1, U6.33 (VBAT_IN), U6.36 (VDD_IO); also elsewhere on the board
BT_RX: TP4.1, U6.14 (BT_RX/PIO4); also elsewhere on the board
BT_TX: TP3.1, U6.13 (BT_TX/PIO5); also elsewhere on the board
GND: C20.2, C21.2, C22.2, C23.2, C24.2, C26.2, C28.1, D4.2 (A2), J3.2, Q1.2 (S), R17.2, TP2.1, U6.1 (GND), U6.22 (GND), U6.32 (GND), U6.50 (GND), U6.52 (GND); also elsewhere on the board
P3_DM: R15.1; also elsewhere on the board
P3_DP: R14.1; also elsewhere on the board
SPK_LN: U6.48 (SPK_LN); also elsewhere on the board
SPK_LP: U6.49 (SPK_LP); also elsewhere on the board
SPK_RN: U6.46 (SPK_RN); also elsewhere on the board
SPK_RP: U6.47 (SPK_RP); also elsewhere on the board
VBUS: C22.1, R19.1, R20.1, U6.29 (VCHG_SENSE), U6.39 (VCC_CHG); also elsewhere on the board

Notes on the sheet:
BLUETOOTH MODULE Feasycom FSC-BT1026C: powered from BT_3V3 (VBAT_IN, VDD_IO); VCC_CHG on 5 V for its USB (charger stays off, its default)
POWER-ON: Feasycom "Option One" delayed start (SYS_CTRL low > 100 ms after BT_3V3, then high), 2N7002 for their 2SK3018
STATUS LEDS on the module's open-drain LED pads (tolerant to 7 V, so fed from 5 V): LED0 blinks while pairing, LED1 on when connected
EXTERNAL CABIN MICROPHONE on MIC_L (the input calls use): electret, biased from MIC_BIAS (Feasycom reference "MIC")
TEST PADS: Feasycom update / debug (VDD, SPI, UART) and the spare control pins

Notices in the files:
README.md:
Licence:
[CC BY-NC-SA 4.0](LICENSE): build it, change it and share it with credit, under the same licence, not for sale. For
commercial use, ask first.
